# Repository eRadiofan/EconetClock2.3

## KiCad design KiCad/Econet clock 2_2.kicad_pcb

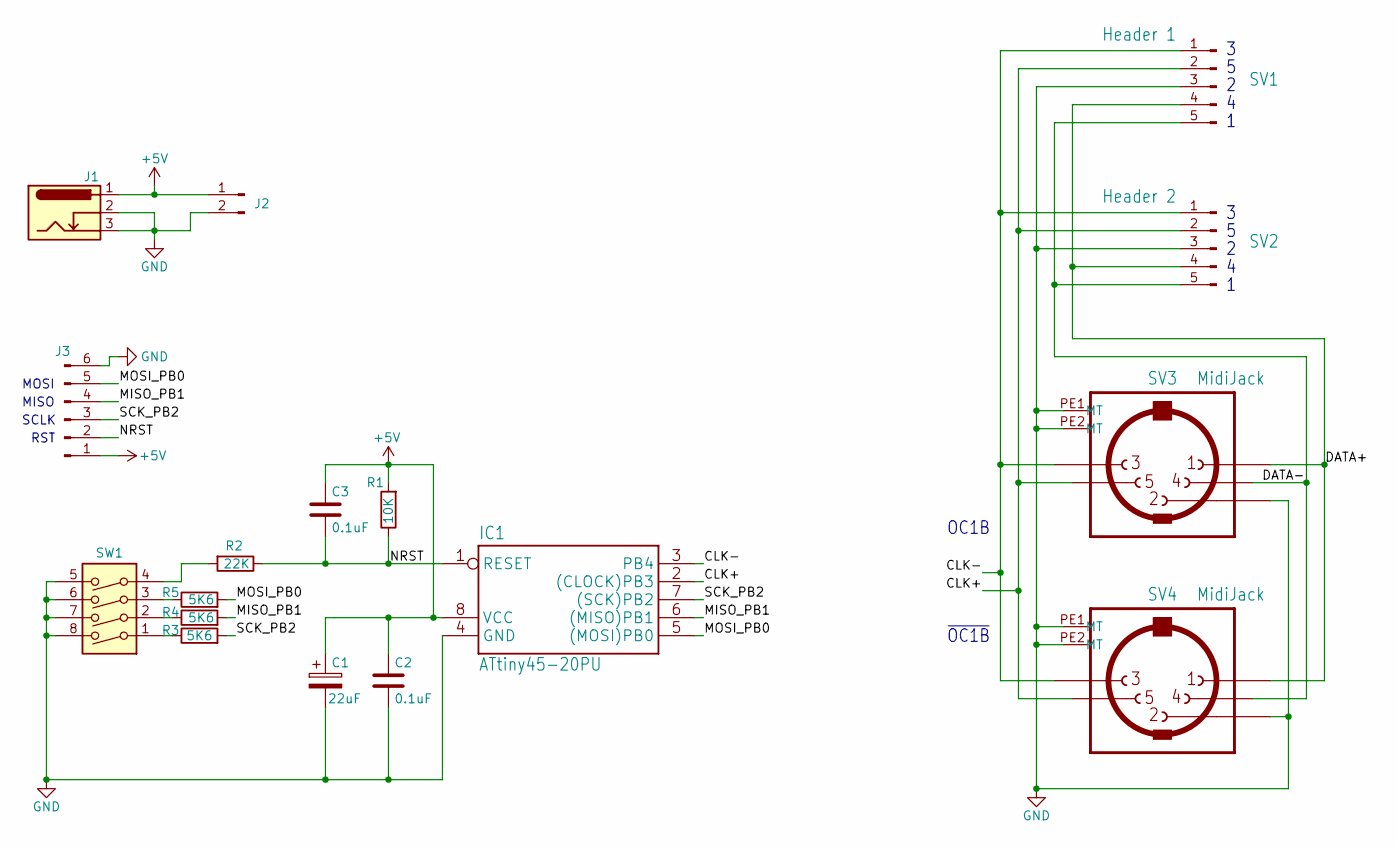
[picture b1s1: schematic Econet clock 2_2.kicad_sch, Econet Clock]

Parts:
C1: 22uF; CP_Radial_D5.0mm_P2.00mm
C2, C3: 0.1uF; C_Disc_D4.7mm_W2.5mm_P5.00mm
IC1: ATtiny45-20PU; DIP-8_W7.62mm_Socket_LongPads
J1: Conn_01x02_Male; BarrelJack_Horiz_14x9
J2: Conn_01x02_Pin; PinHeader_1x02_P2.54mm_Vertical
J3: Conn_01x06_Pin; PinHeader_1x06_P2.54mm_Vertical
R1: 10K; R_Axial_DIN0204_L3.6mm_D1.6mm_P7.62mm_Horizontal
R2: 22K; R_Axial_DIN0204_L3.6mm_D1.6mm_P7.62mm_Horizontal
R3, R4, R5: 5K6; R_0805_2012Metric_Pad1.20x1.40mm_HandSolder
SV1: Header 1; PinHeader_1x05_P2.54mm_Vertical
SV2: Header 2; PinHeader_1x05_P2.54mm_Vertical
SV3, SV4: MidiJack; MidiConnector
SW1: SW_DIP_x04; SW_DIP_SPSTx04_Slide_9.78x12.34mm_W7.62mm_P2.54mm

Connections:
+5V: C1.1, C2.1, C3.1, IC1.8 (VCC), J1.1, J2.1, J3.1, R1.2
/CLK+: IC1.2 ((CLOCK)PB3), SV1.2, SV2.2, SV3.5, SV4.5
/CLK-: IC1.3 (PB4), SV1.1, SV2.1, SV3.3, SV4.3
/DATA+: SV1.4, SV2.4, SV3.1, SV4.1
/DATA-: SV1.5, SV2.5, SV3.4, SV4.4
/MISO_PB1: IC1.6 ((MISO)PB1), J3.4, R4.2
/MOSI_PB0: IC1.5 ((MOSI)PB0), J3.5, R5.2
/NRST: C3.2, IC1.1 (RESET), J3.2, R1.1, R2.1
/SCK_PB2: IC1.7 ((SCK)PB2), J3.3, R3.2
GND: C1.2, C2.2, IC1.4 (GND), J1.2, J1.3, J2.2, J3.6, SV1.3, SV2.3, SV3.2, SV3.PE1 (MT), SV3.PE2 (MT), SV4.2, SV4.PE1 (MT), SV4.PE2 (MT), SW1.5, SW1.6, SW1.7, SW1.8
unnamed: R2.2, SW1.4
unnamed: R3.1, SW1.1
unnamed: R4.1, SW1.2
unnamed: R5.1, SW1.3

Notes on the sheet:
MISO
OC1B
SCLK
RST
MOSI
~{OC1B}

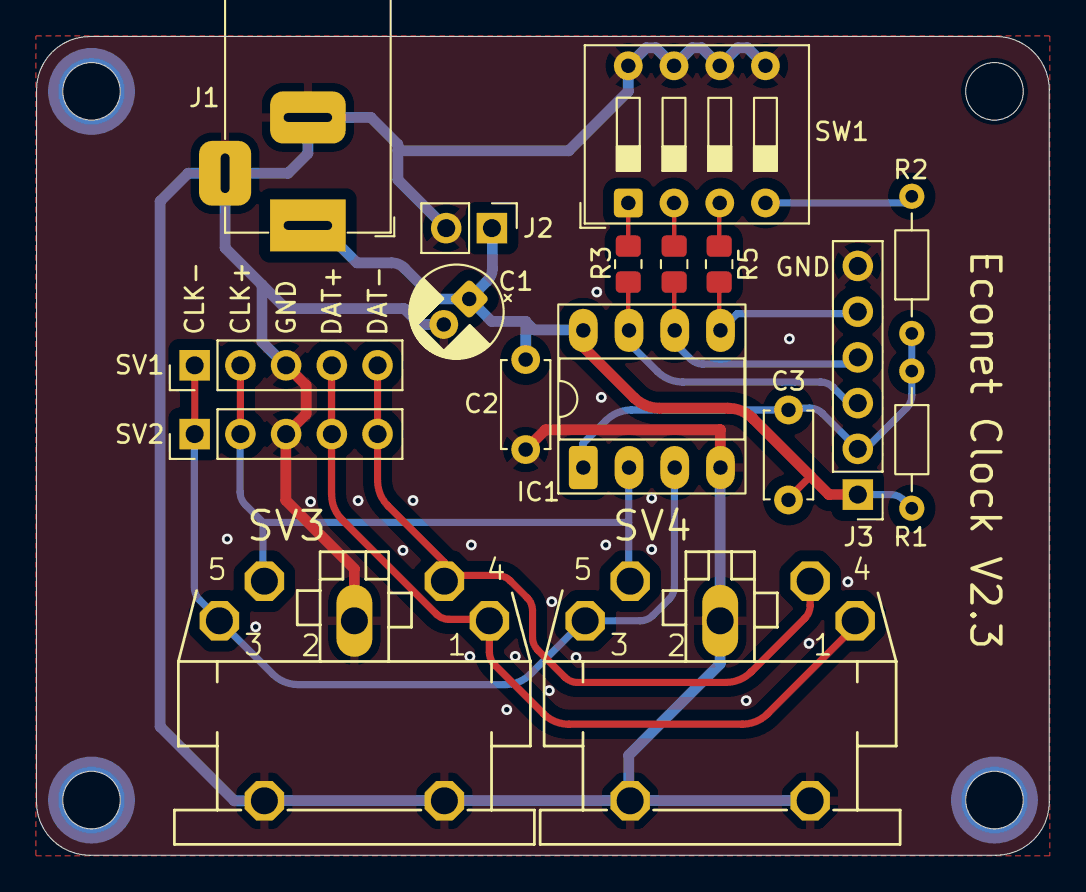
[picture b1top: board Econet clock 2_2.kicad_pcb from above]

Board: 2 copper layers, 56.3 x 45.5 mm, 17 parts (0 on the bottom side), 14 nets.

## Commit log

2025-11-26 Conversion to KiCad, DIP sw 4 is now functional, DIP switch selection no longer prevents programming, PCB is now dual layer with optimised traks
2025-12-06 Use of 4th DIP provides better selection of frequencies
2025-12-13 Updated data polarity markings, increased decoupling capacitance

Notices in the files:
KiCad/Econet clock 2_2.kicad_sch:
Licensing (CC BY 4.0)
(c) 2016 Simon Inns
